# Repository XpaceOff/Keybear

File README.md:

# Keybear

## Directory Structure

- firmware: contain files to setup the firmware of the board.
  - kmk: [kmk firmware](https://github.com/KMKfw/kmk_firmware) config files.
- keybear-chocolate: all files used to create the chocolate version of the board.
  - case:
    - gcode_and_obj: Files used to print the case
    - plasticity_archive: old versions of the plasticity file.
    - keybear-choco_case_slim.plasticity: Latest plasticity file.
- kicad_footprints: footprints used in my kicad projects.

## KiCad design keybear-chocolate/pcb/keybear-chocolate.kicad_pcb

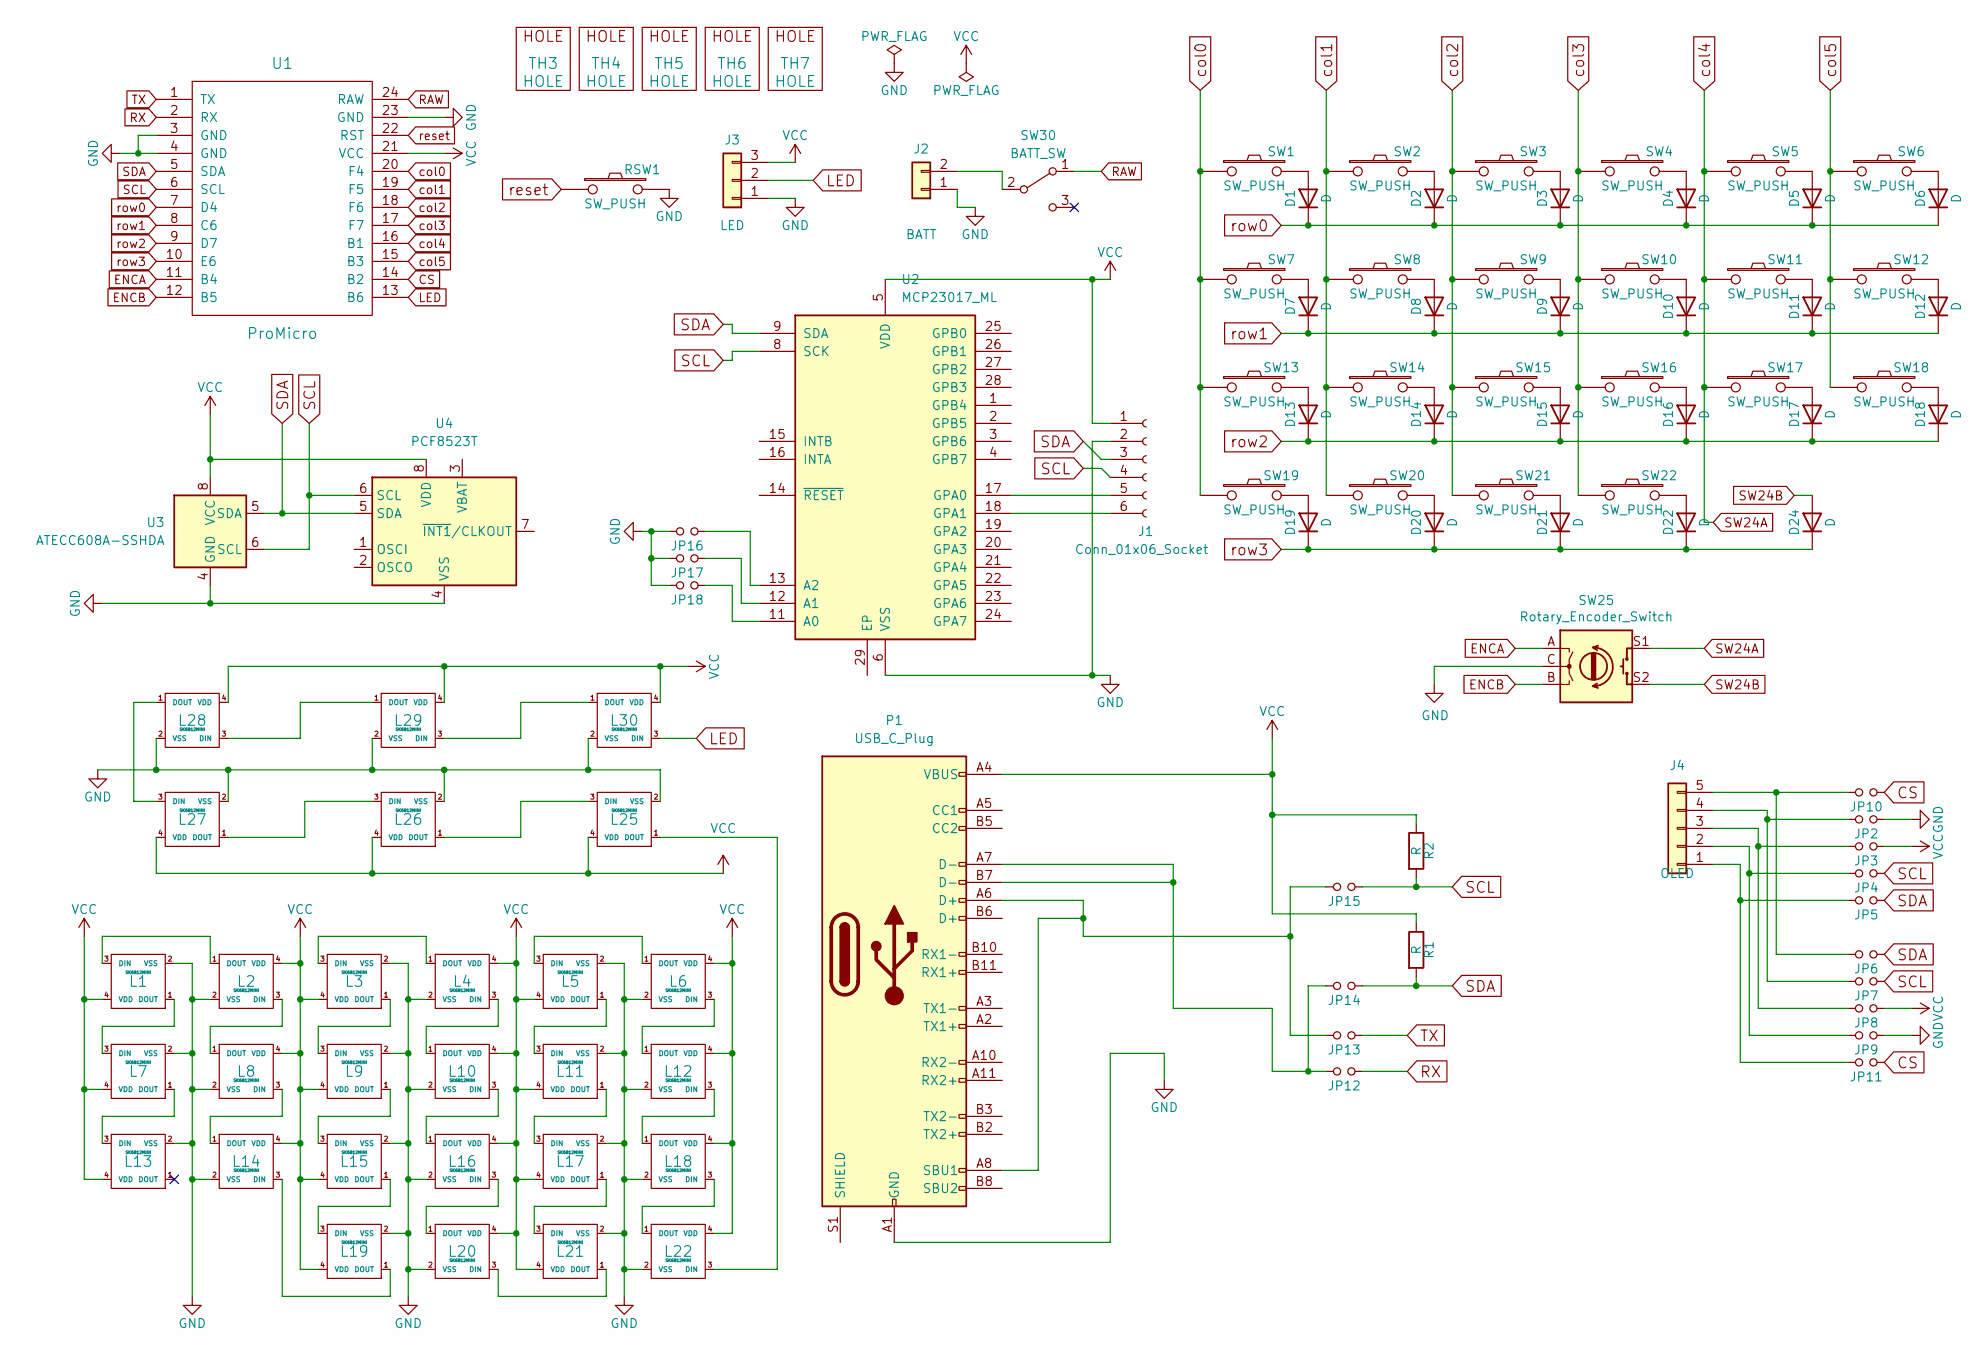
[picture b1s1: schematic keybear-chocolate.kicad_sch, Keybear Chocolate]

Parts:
D1, D2, D3, D4, D5, D6, D7, D8, D9, D10, D11, D12, D13, D14, D15, D16, D17, D18, D19, D20, D21, D22, D24: D; D3_SMD
J1: Conn_01x06_Socket; xo_header-0,5-6-2,5-V-SMD_1x06-1MP_P2.50mm
J2: BATT; StripBATT_xo
J3: LED; StripLED_xo
J4: OLED; OLED_xo_5pins
JP2, JP3, JP4, JP5, JP6, JP7, JP8, JP9, JP10, JP11, JP12, JP13, JP14, JP15, JP16, JP17, JP18: Jumper
L1, L2, L3, L4, L5, L6, L7, L8, L9, L10, L11, L12, L13, L14, L15, L16, L17, L18, L19, L20, L21, L22, L25, L26, L27, L28, L29, L30: SK6812MINI; SK6812MINI_xo_v02
P1: USB_C_Plug; USB_C_Receptacle_G-Switch_GT-USB-7010ASV
R1, R2: R; R_1206_3216Metric
RSW1: SW_PUSH; ResetSW
SW1, SW2, SW3, SW4, SW5, SW6, SW7, SW8, SW9, SW10, SW11, SW12, SW13, SW14, SW15, SW16, SW17, SW18, SW19, SW20, SW21: SW_PUSH; Choc_Hotswap
SW22: SW_PUSH; Choc_Hotswap_1.5u
SW25: Rotary_Encoder_Switch; RotaryEncoder_Alps_EC11E-Switch_Vertical_H20mm-keebio_modif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
SW30: BATT_SW; SW_SPDT_PCM12_2sides_xo
TH3, TH4, TH5, TH6, TH7: HOLE; HOLE_M2_TH
U1: ProMicro; ProMicro_xo
U2: MCP23017_ML; QFN-28-1EP_6x6mm_P0.65mm_EP4.25x4.25mm
U3: ATECC608A-SSHDA; SOIC-8_3.9x4.9mm_P1.27mm
U4: PCF8523T; SOIC-8_3.9x4.9mm_P1.27mm

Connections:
CS: JP10.1, JP11.1, U1.14 (B2)
ENCA: U1.11 (B4); also elsewhere on the board
ENCB: U1.12 (B5); also elsewhere on the board
GND: J1.2, J2.1, J3.1, JP2.1, JP9.1, JP16.2, JP17.2, JP18.2, L1.2 (VSS), L2.2 (VSS), L3.2 (VSS), L4.2 (VSS), L5.2 (VSS), L6.2 (VSS), L7.2 (VSS), L8.2 (VSS), L9.2 (VSS), L10.2 (VSS), L11.2 (VSS), L12.2 (VSS), L13.2 (VSS), L14.2 (VSS), L15.2 (VSS), L16.2 (VSS), L17.2 (VSS), L18.2 (VSS), L19.2 (VSS), L20.2 (VSS), L21.2 (VSS), L22.2 (VSS), L25.2 (VSS), L26.2 (VSS), L27.2 (VSS), L28.2 (VSS), L29.2 (VSS), L30.2 (VSS), P1.A1 (GND), P1.A12 (GND), P1.B1 (GND), P1.B12 (GND), RSW1.2, U1.3 (GND), U1.4 (GND), U1.23 (GND), U2.6 (VSS), U3.4 (GND), U4.4 (VSS); also elsewhere on the board
LED: J3.2, L30.3 (DIN), U1.13 (B6)
unnamed: D1.2 (A), SW1.2
unnamed: D2.2 (A), SW2.2
unnamed: D3.2 (A), SW3.2
unnamed: D4.2 (A), SW4.2
unnamed: D5.2 (A), SW5.2
unnamed: D6.2 (A), SW6.2
unnamed: D7.2 (A), SW7.2
unnamed: D8.2 (A), SW8.2
unnamed: D9.2 (A), SW9.2
unnamed: D10.2 (A), SW10.2
unnamed: D11.2 (A), SW11.2
unnamed: D12.2 (A), SW12.2
unnamed: D13.2 (A), SW13.2
unnamed: D14.2 (A), SW14.2
unnamed: D15.2 (A), SW15.2
unnamed: D16.2 (A), SW16.2
unnamed: D17.2 (A), SW17.2
unnamed: D18.2 (A), SW18.2
unnamed: D19.2 (A), SW19.2
unnamed: D20.2 (A), SW20.2
unnamed: D21.2 (A), SW21.2
unnamed: D22.2 (A), SW22.2
unnamed: J1.5, U2.17 (GPA0)
unnamed: J1.6, U2.18 (GPA1)
unnamed: J2.2, SW30.2 (B)
unnamed: J4.1, JP5.2, JP11.2
unnamed: J4.2, JP4.2, JP9.2
unnamed: J4.3, JP3.2, JP8.2
unnamed: J4.4, JP2.2, JP7.2
unnamed: J4.5, JP6.2, JP10.2
unnamed: JP12.2, JP14.2, P1.A7 (D-), P1.B7 (D-)
unnamed: L1.3 (DIN), L2.1 (DOUT)
unnamed: L1.1 (DOUT), L7.3 (DIN)
unnamed: L2.3 (DIN), L8.1 (DOUT)
unnamed: L3.3 (DIN), L4.1 (DOUT)
unnamed: L3.1 (DOUT), L9.3 (DIN)
unnamed: L5.3 (DIN), L6.1 (DOUT)
unnamed: L10.3 (DIN), L16.1 (DOUT)
unnamed: L4.3 (DIN), L10.1 (DOUT)
unnamed: L5.1 (DOUT), L11.3 (DIN)
unnamed: L11.1 (DOUT), L17.3 (DIN)
unnamed: L12.3 (DIN), L18.1 (DOUT)
unnamed: L6.3 (DIN), L12.1 (DOUT)
unnamed: L7.1 (DOUT), L13.3 (DIN)
unnamed: L14.3 (DIN), L19.1 (DOUT)
unnamed: L8.3 (DIN), L14.1 (DOUT)
unnamed: L9.1 (DOUT), L15.3 (DIN)
unnamed: L15.1 (DOUT), L19.3 (DIN)
unnamed: L16.3 (DIN), L20.1 (DOUT)
unnamed: L17.1 (DOUT), L21.3 (DIN)
unnamed: L18.3 (DIN), L22.1 (DOUT)
unnamed: L20.3 (DIN), L21.1 (DOUT)
unnamed: L22.3 (DIN), L25.1 (DOUT)
unnamed: L25.3 (DIN), L26.1 (DOUT)
unnamed: L26.3 (DIN), L27.1 (DOUT)
unnamed: L27.3 (DIN), L28.1 (DOUT)
unnamed: L28.3 (DIN), L29.1 (DOUT)
unnamed: L29.3 (DIN), L30.1 (DOUT)
unnamed: JP13.2, JP15.2, P1.A6 (D+), P1.A8 (SBU1)
unnamed: JP18.1, U2.11 (A0)
unnamed: JP17.1, U2.12 (A1)
unnamed: JP16.1, U2.13 (A2)
RAW: SW30.1 (A), U1.24 (RAW)
RX: JP12.1, U1.2 (RX)
SCL: J1.4, JP4.1, JP7.1, JP15.1, R2.2, U1.6 (SCL), U2.8 (SCK), U3.6 (SCL), U4.6 (SCL)
SDA: J1.3, JP5.1, JP6.1, JP14.1, R1.2, U1.5 (SDA), U2.9 (SDA), U3.5 (SDA), U4.5 (SDA)
SW24A: SW5.1, SW11.1, SW17.1, U1.16 (B1); also elsewhere on the board
SW24B: D24.2 (A); also elsewhere on the board
TX: JP13.1, U1.1 (TX)
VCC: J1.1, J3.3, JP3.1, JP8.1, L1.4 (VDD), L2.4 (VDD), L3.4 (VDD), L4.4 (VDD), L5.4 (VDD), L6.4 (VDD), L7.4 (VDD), L8.4 (VDD), L9.4 (VDD), L10.4 (VDD), L11.4 (VDD), L12.4 (VDD), L13.4 (VDD), L14.4 (VDD), L15.4 (VDD), L16.4 (VDD), L17.4 (VDD), L18.4 (VDD), L19.4 (VDD), L20.4 (VDD), L21.4 (VDD), L22.4 (VDD), L25.4 (VDD), L26.4 (VDD), L27.4 (VDD), L28.4 (VDD), L29.4 (VDD), L30.4 (VDD), P1.A4 (VBUS), P1.A9 (VBUS), P1.B4 (VBUS), P1.B9 (VBUS), R1.1, R2.1, U1.21 (VCC), U2.5 (VDD), U3.8 (VCC), U4.8 (VDD)
col0: SW1.1, SW7.1, SW13.1, SW19.1, U1.20 (F4)
col1: SW2.1, SW8.1, SW14.1, SW20.1, U1.19 (F5)
col2: SW3.1, SW9.1, SW15.1, SW21.1, U1.18 (F6)
col3: SW4.1, SW10.1, SW16.1, SW22.1, U1.17 (F7)
col5: SW6.1, SW12.1, SW18.1, U1.15 (B3)
reset: RSW1.1, U1.22 (RST)
row0: D1.1 (K), D2.1 (K), D3.1 (K), D4.1 (K), D5.1 (K), D6.1 (K), U1.7 (D4)
row1: D7.1 (K), D8.1 (K), D9.1 (K), D10.1 (K), D11.1 (K), D12.1 (K), U1.8 (C6)
row2: D13.1 (K), D14.1 (K), D15.1 (K), D16.1 (K), D17.1 (K), D18.1 (K), U1.9 (D7)
row3: D19.1 (K), D20.1 (K), D21.1 (K), D22.1 (K), D24.1 (K), U1.10 (E6)

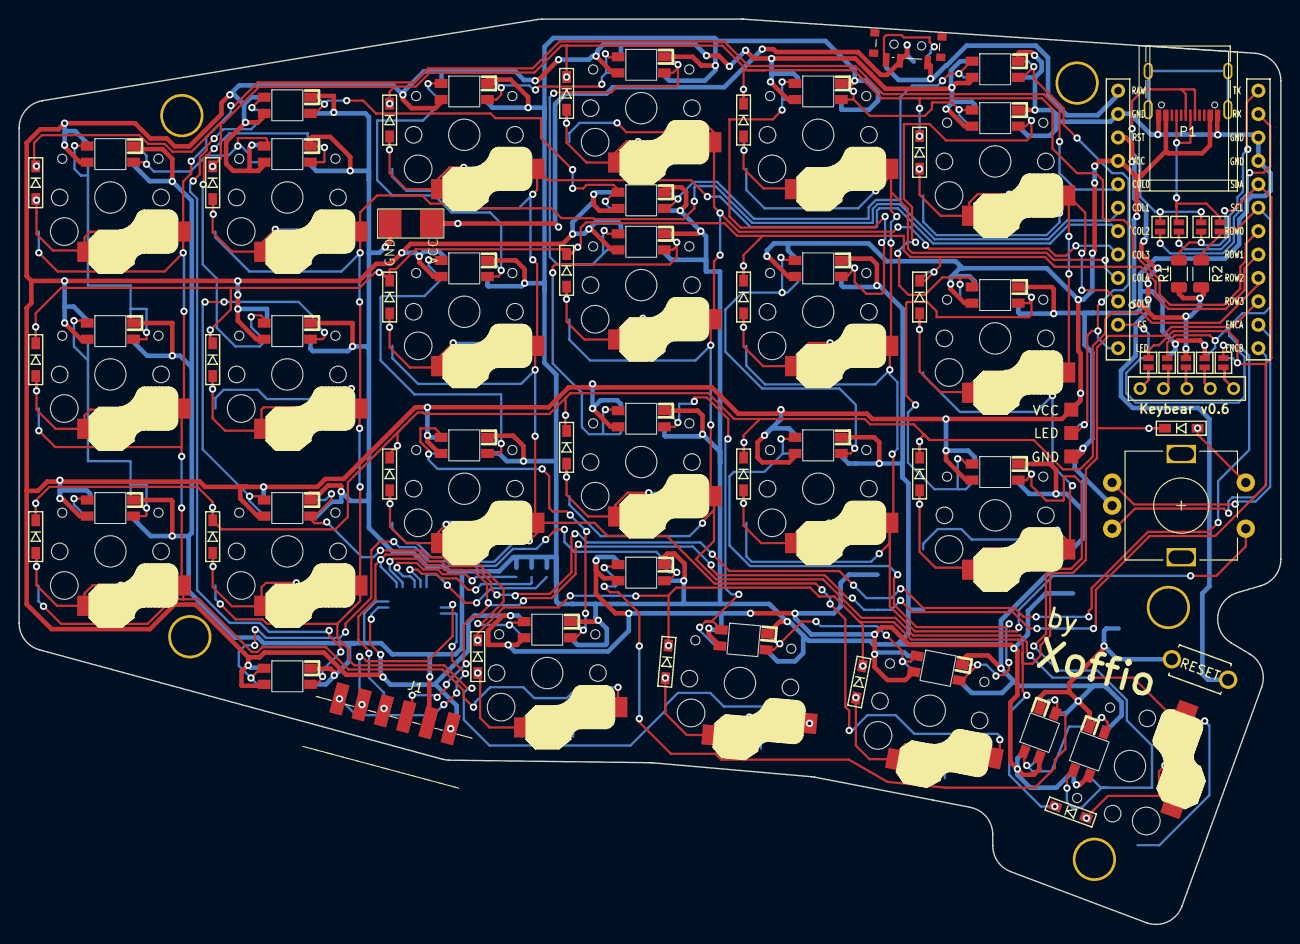
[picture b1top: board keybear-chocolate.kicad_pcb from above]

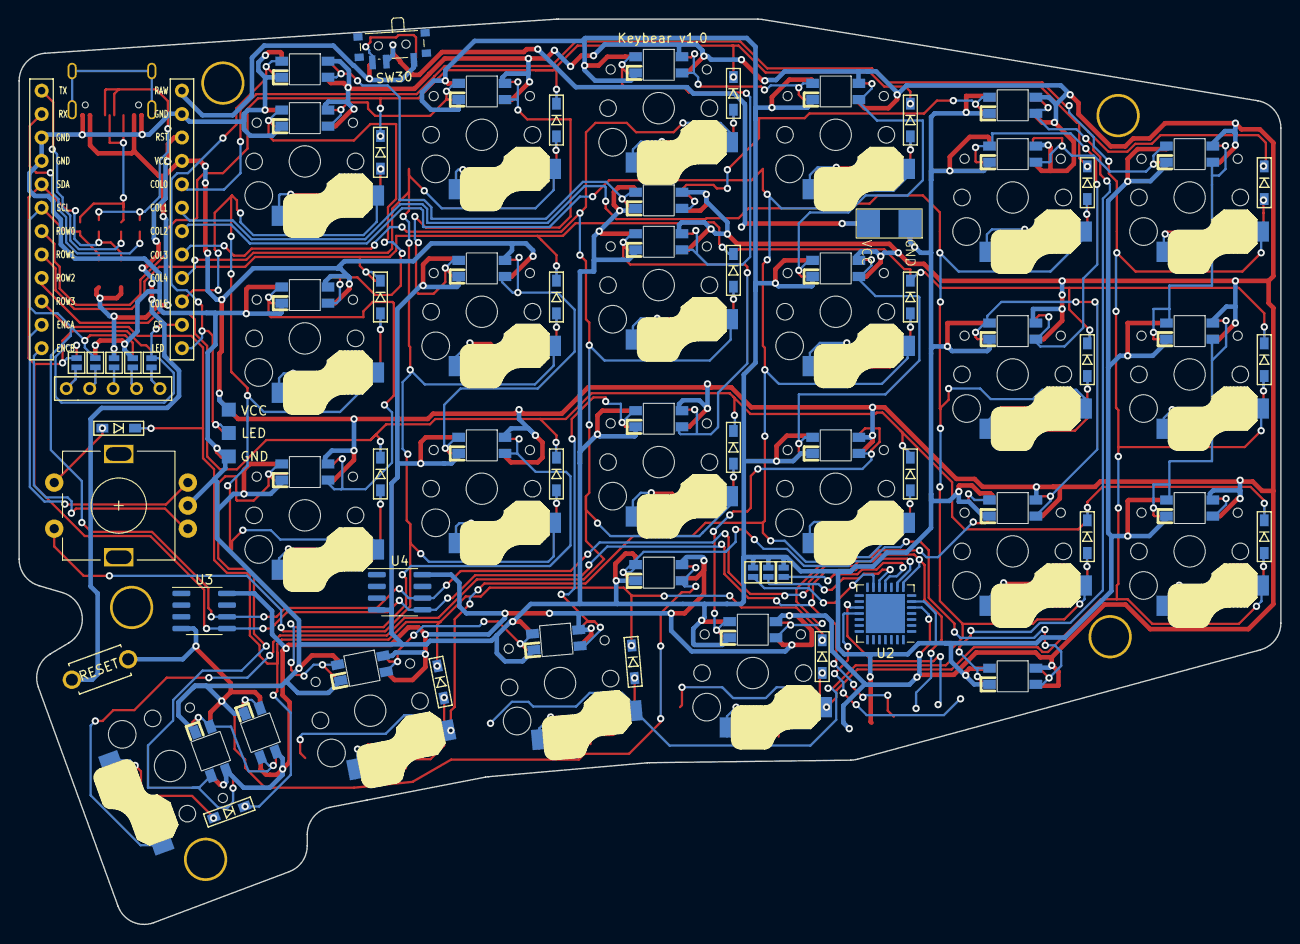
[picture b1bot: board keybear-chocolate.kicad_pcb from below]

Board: 2 copper layers, 136.9 x 98.2 mm, 109 parts (12 on the bottom side), 85 nets.

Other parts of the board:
SW24: Rotary_Encoder_Switch; RotaryEncoder_Alps_EC11E-Switch_Vertical_H20mm-keebio_modif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

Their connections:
ENCA: SW24.A; also elsewhere on the board
ENCB: SW24.B; also elsewhere on the board
GND: SW24.C; also elsewhere on the board
SW24A: SW24.S1; also elsewhere on the board
SW24B: SW24.S2; also elsewhere on the board

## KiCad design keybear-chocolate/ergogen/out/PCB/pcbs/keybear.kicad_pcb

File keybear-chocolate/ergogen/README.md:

I downloaded Ergogen in a folder called `tmp` in the upper directory.

projects
  |-- tmp
  | |-- ergogen
  |-- Keybear

to compile the Kicad files from the Ergogen config file I do:

```bash
cd Keybear

# For PCB
node ..\tmp\ergogen\src\cli.js keybear-chocolate\ergogen\ -o keybear-chocolate\ergogen\out\PCB

# For Plate
node ..\tmp\ergogen\src\cli.js keybear-chocolate\ergogen\ -o keybear-chocolate\ergogen\out\Plate
```

> [!Note] 
> To generate the plate you will need to change the value of `pcbs.keybear.outlines.main.outline`
> to `combo`. Generate the plate and remember to set it back to `plate`

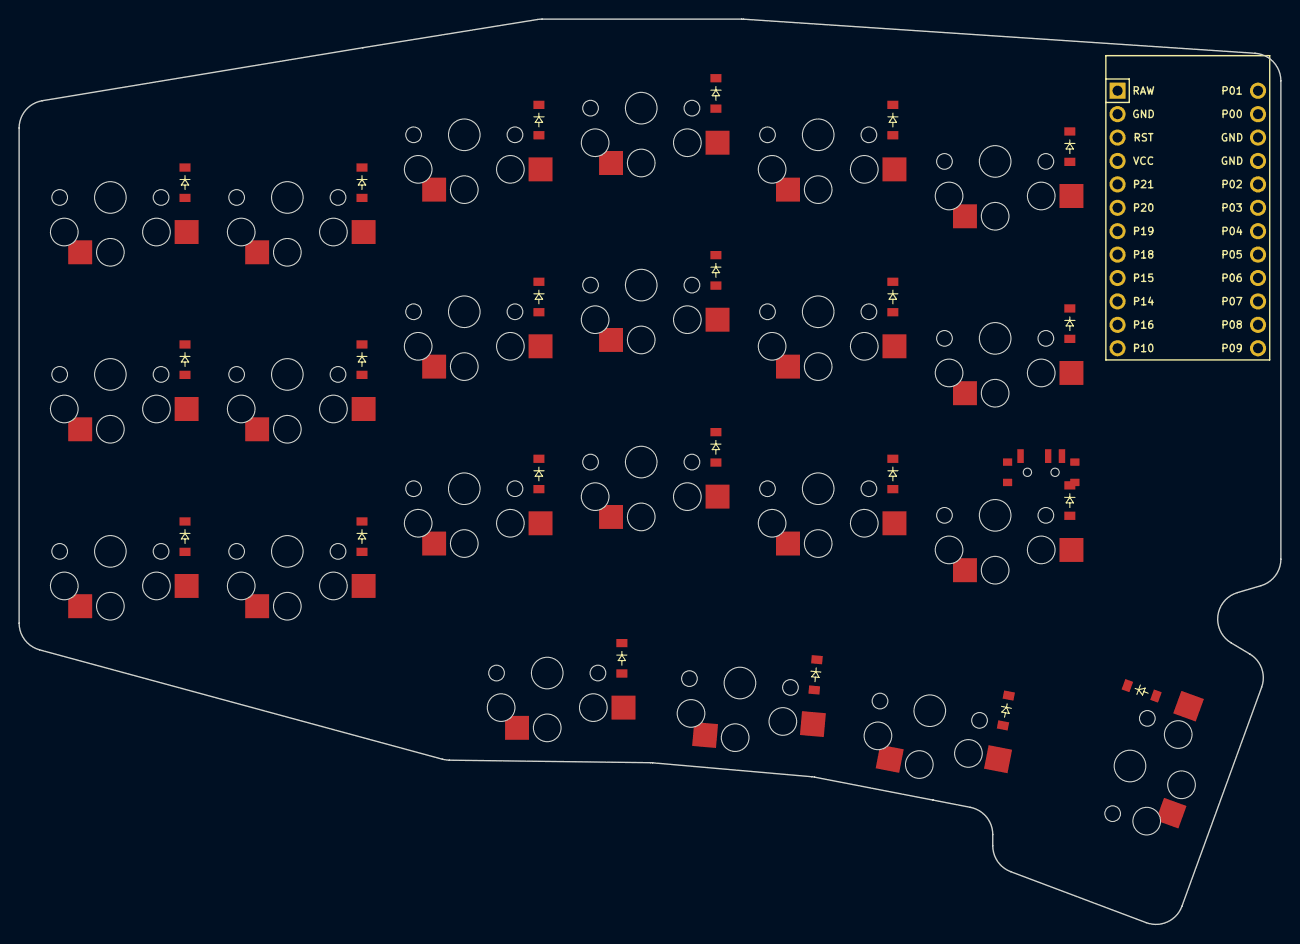
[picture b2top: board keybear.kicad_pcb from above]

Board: 2 copper layers, 136.9 x 98.2 mm, 45 parts (0 on the bottom side), 23 nets, no tracks yet.

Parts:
D1, D2, D3, D4, D5, D6, D7, D8, D9, D10, D11, D12, D13, D14, D15, D16, D17, D18, D19, D20, D21, D22: ComboDiode
MCU1: ProMicro
S1, S2, S3, S4, S5, S6, S7, S8, S9, S10, S11, S12, S13, S14, S15, S16, S17, S18, S19, S20, S21, S22: PG1350

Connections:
GND: MCU1.2, MCU1.15, MCU1.16
ctrl_cluster: D20.2, S20.2
index_bottom: D13.2, S13.2
index_home: D14.2, S14.2
index_top: D15.2, S15.2
inner_bottom: D16.2, S16.2
inner_home: D17.2, S17.2
inner_top: D18.2, S18.2
layer_cluster: D21.2, S21.2
middle_bottom: D10.2, S10.2
middle_home: D11.2, S11.2
middle_top: D12.2, S12.2
opt_cluster: D19.2, S19.2
outer_bottom: D1.2, S1.2
outer_home: D2.2, S2.2
outer_top: D3.2, S3.2
pinky_bottom: D4.2, S4.2
pinky_home: D5.2, S5.2
pinky_top: D6.2, S6.2
ring_bottom: D7.2, S7.2
ring_home: D8.2, S8.2
ring_top: D9.2, S9.2
space_cluster: D22.2, S22.2

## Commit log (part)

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2023-08-28 Initial files
2023-08-28 gitignore added
2023-08-29 updating keys
2023-08-30 Initial ergogen file
2023-08-31 updating spaces
2023-09-01 adding the mod row
2023-09-02 Adding outlines
2023-09-02 adding pcb components
2023-09-02 adjust switch pos
2023-09-03 updated gitignore
2023-09-04 diodes added. pcb plate updated
2023-09-04 right plate added in comments
2023-09-04 updated latest kicad files
2023-09-04 OLED port updated to 5 pins
    OLED port updated to 5 pins to support NiceView! out of the box
2023-09-04 OLED Resistence removed
2023-09-04 rotary button mapped
2023-09-04 set the plate horizontal for better working
2023-09-04 set plate horizontal for better working
2023-09-06 ergogen config file renamed to be used with ergogen v4
2023-09-06 ergogen footprints added. WIP
2023-09-08 footprints updated
2023-09-08 pcm12 added to ergogen's config file
    This is only added to be able to imported into the kicad file i have been working on
2023-09-08 latest ergogen output
2023-09-08 keys in place
2023-09-08 latest schematics
2023-09-09 custom kicad footprints added
2023-09-09 using custom footprints
    using custom footprints for leds and oled display
2023-09-09 positioned leds
2023-09-09 diodes organized and backlights set
2023-09-09 custom promicro added
2023-09-09 custom footprint of promicro
2023-09-10 Battery pins footprint made
2023-09-10 update schematics with new batt pins footprint
2023-09-10 small changes to pcb
2023-09-10 outline updated
    updated the outline to fit the promicro
2023-09-10 custom strip LED added
2023-09-10 power switch and strip batt added/mod
2023-09-11 Promicro updated and other small changes
2023-09-11 trrs i2c deleted
    i don't think i am going to need the trrs i2c communication. Using USART Half-duplex instead. It only uses one pin (data)
2023-09-12 first tracks. diodes repo
2023-09-13 key were re-arrange. more tracks added
2023-09-14 adding more traces
2023-09-15 adding more tracks
2023-09-19 more tracks added
2023-09-21 finished with keys LEG's tracks
2023-09-22 finishing back leds
2023-09-23 LEDs connected
2023-09-23 OLED Jumper fixed and connected
2023-09-23 batt strip footprint updated.
    batt strip in bigger
2023-09-23 batt strip connection updated. tracks made
2023-09-23 data and batt switch connections made
2023-09-23 diodes back plate connections added
2023-09-23 some DRC errors fixed.
    Missing connectection fixed
2023-09-23 LED footprint updated
2023-09-23 removec LEDs holes to use the new footprint
2023-09-23 LEDs footprint updated an DRC errors fixed
2023-09-24 gerber options updated
2023-09-26 adding holes to the pcb
2023-09-27 holes added
2023-09-27 ground layer added
2023-09-27 fix thermal errors
2023-09-27 text added to the pcb
2023-09-28 set right gerber values to send to jlcpcb
2023-10-01 added initial file for the plate
2023-10-01 generated Gerber files added
2023-10-01 creating case model
2023-10-07 added missing diode
2023-10-07 updated diode, fixed ground filled layer and other small fixes
2023-10-08 test code for rp2040-zero
2023-10-08 initial code for blok. Left pcb working with under leds
2023-10-08 3d models used to make the case
2023-10-08 case updated
2023-10-09 different version of case. no spcase for battery
2023-10-09 slim version of the case updated
2023-10-09 small changes in the code
2023-10-09 first gcode version
2023-10-09 files for prusa added
2023-10-10 updating the case
2023-10-11 model updated
2023-10-11 I don't think i will need the .3mf files
2023-10-11 gcode files updated
2023-10-11 obj files updated
2023-10-12 upper right hole moved to a better position
2023-10-12 more leds solded into the board
2023-10-13 encoder support ^& other small changes
2023-10-14 setting up right side
2023-10-15 updating case and makig the right one
2023-10-16 testing adding layers
2023-10-17 adding holdtap and more keys to layers
2023-10-18 updating the keys
2023-10-18 updaing firmware keys
2023-10-18 adding gui swap
2023-10-19 cleaning keymap
2023-10-19 adding config layer ^& modifying rgb
2023-10-20 small firware changes.. RGB_TOG bug present
2023-10-22 RGB update in the firmware
2023-10-22 added layer fix
2023-10-22 changing color of rgb when layer changes
2023-10-22 firmware reacting to lock status
2023-10-22 firmware - keyboard is now able to record a seq of keys
2023-10-22 caps lock tested and working
2023-10-23 set dft layer when in confi layer, and key pressed is non-number or arrow
2023-10-23 function layer added
2023-10-23 arrow layer added
2023-10-24 adding keypad layer and other key mods
2023-10-25 get caps lock status when booting
2023-10-25 layer status on when booting
2023-10-29 adding rgb to cgswap status
2023-10-29 small changes
2023-10-30 deleting key and making the keyboard more compact - ergogen
2023-10-31 changes to the pcb outline
2023-11-05 making the pcb more compact and removing key, and other general changes
2023-11-05 small changes to the outline onthe upper side of the pcb
2023-11-05 batt switch re-connected
2023-11-06 re-connecting one of the under RGB
2023-11-07 re-connecting more keys and leds
2023-11-07 re-connections
2023-11-08 all keys and leds re-connected
2023-11-08 reset button is back.
    reset button is back but i might removed it later. TBD
2023-11-09 updated with new connections to work with blok
2023-11-09 reconnection of promicro pins
2023-11-10 resistors added back
2023-11-11 moving LED ping. Adding/rename RX/TX
2023-11-11 board will be able to do uart or i2c communication between boards
2023-11-13 shift tracks around TRRS to start makind a modular mini-pcb
2023-11-15 making space for the small pcb
2023-11-16 adding possible future pads
2023-11-17 adding a pcb for the trrs connector
2023-11-18 BEFORE USBC
    I decided to do usbc instead of modular, just for now, to keep it simple...
2023-11-18 usb-c added - WIP
2023-11-20 usb-c rx-tx connections added
2023-11-21 trrs deleted. usb-c connected - v0.5
2023-11-24 making space at the top left to add exteranl GPIO pins
2023-11-24 adding MPC23P17_ML to add the external GPIO pins
2023-11-25 connecting MPC23P17_ML
2023-11-27 adding ATECC608A-SSHDA crypto chip
2023-11-28 adding PCF8523 (Real Time Clock)
2023-11-29 creating connections for the rtc and crypto chip
2023-12-01 crypto chip connected
2023-12-05 time chip connected. tracks extended
2023-12-14 adding smd header. Reset button moved
2023-12-19 connecting chip to extend ports
2023-12-20 more connections added
2024-01-16 connections added ^& DRC ran
    Keybear v0.6
2024-01-16 ignoring wrl files
2024-01-30 gerber files updated
2024-02-25 organize files a little bit better
2024-02-25 Lets have two outputs. One for the pcb ^& anotherone for the plate
2024-02-25 added new outline for the key holes
2024-02-25 updating the plate
2024-02-25 keyholes set to 14mmx14mm
2024-02-26 v0.6.0 step files updated
2024-02-26 creating new case for v0.6.0
2024-02-27 pcb added. creating initial core lines to extrude case
2024-03-03 case surround added
2024-03-03 update plate pcb
2024-03-03 .15mm offset added between the pcb and the case
2024-03-04 switch added. lid updated
2024-04-13 lid updated. screw models added
2024-04-21 gcodes organized. obj for v0.6.0 updated
2025-05-08 preparing blok firmware for v0.6.0 hardware upgrade
2025-05-10 Updated model and readme
2025-05-11 firmware changes
    - Clean up code
2025-05-12 Docs and comments updated
    - Tested KMK version c617749
2025-05-25 v0.6.0 model updated
2026-03-01 Added svg plate
